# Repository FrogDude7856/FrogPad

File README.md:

# FrogPad
A 12-key hackpad for music with a .91in OLED and a frog-shaped case.

# Features
- Volume and music playback control as default
- 12 Cherry MX compatable mechanical keys
- An OLED that (hopefully) displays your current audio playing (TBD) or does whatever else you want it to display
- A frog shaped case
- Direct connection to PC via USB-C for reduced latency
- A delete key in the center to smash to your hearts content

# Credits/Acknolegements
Thank you to:
- the very nice people in the Hack Club Stardance community (namely #hackpad on the slack), for helping me out with my constant questions
- dob9601, who created the OLED display code I am using to run images (https://github.com/dob9601/qmk-oled-api#client-snippet) and to hopefully display music (https://github.com/dob9601/qmk-oled-api#client-snippet)
- QMK's large database of tutorials, for teaching me how to use their software

# BOM
- 1x Seeed XIAO RP2040 microcontroller
- 1x PCB (see Production folder)
- 2x 3D printed parts: 1x TOP and 1x BOTTOM (See Production folder)
- 12x MX-Style mechanical switches
- 12x Keycaps (I am using blank DSA keycaps)
- 12x 1N4148 through-hole diodes
- 1x 0.91in OLED screen
- 4x M3×16mm screws
- 4x M3×5×4mm heatset inserts
- A sodering iron (for assembly)
- Sanity (optional)
- Paint pens/googly eyes for adding case details and labling keys (optional)

# Progress Images (Screenshots of scematic, PCB, and case on their own)

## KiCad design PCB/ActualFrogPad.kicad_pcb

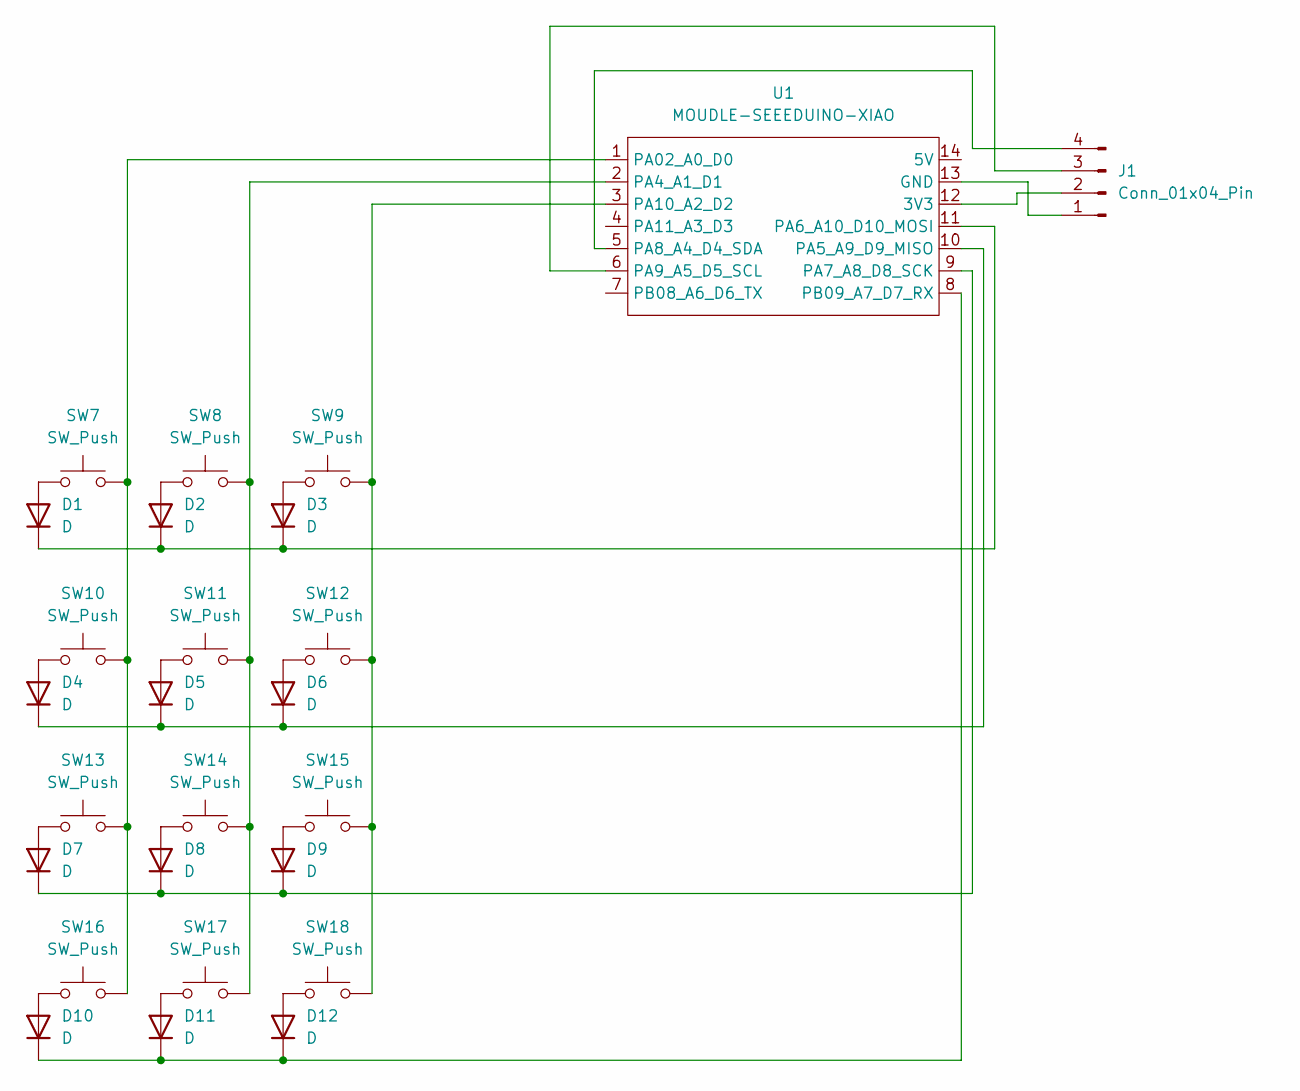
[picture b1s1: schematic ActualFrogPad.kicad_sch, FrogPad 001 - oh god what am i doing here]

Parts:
D1, D2, D3, D4, D5, D6, D7, D8, D9, D10, D11, D12: D; D_DO-35_SOD27_P7.62mm_Horizontal
J1: Conn_01x04_Pin; SSD1306-0.91-OLED-4pin-128x32
SW7, SW8, SW9, SW10, SW11, SW12, SW13, SW14, SW15, SW16, SW17, SW18: SW_Push; SW_Cherry_MX_1.00u_PCB
U1: MOUDLE-SEEEDUINO-XIAO; XIAO-Generic-Hybrid-14P-2.54-21X17.8MM

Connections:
unnamed: D1.2 (A), SW7.1
unnamed: D1.1 (K), D2.1 (K), D3.1 (K), U1.11 (PA6_A10_D10_MOSI)
unnamed: D2.2 (A), SW8.1
unnamed: D3.2 (A), SW9.1
unnamed: D4.2 (A), SW10.1
unnamed: D4.1 (K), D5.1 (K), D6.1 (K), U1.10 (PA5_A9_D9_MISO)
unnamed: D5.2 (A), SW11.1
unnamed: D6.2 (A), SW12.1
unnamed: D7.2 (A), SW13.1
unnamed: D7.1 (K), D8.1 (K), D9.1 (K), U1.9 (PA7_A8_D8_SCK)
unnamed: D8.2 (A), SW14.1
unnamed: D9.2 (A), SW15.1
unnamed: D10.2 (A), SW16.1
unnamed: D10.1 (K), D11.1 (K), D12.1 (K), U1.8 (PB09_A7_D7_RX)
unnamed: D11.2 (A), SW17.1
unnamed: D12.2 (A), SW18.1
unnamed: J1.1, U1.13 (GND)
unnamed: J1.2, U1.12 (3V3)
unnamed: J1.3, U1.6 (PA9_A5_D5_SCL)
unnamed: J1.4, U1.5 (PA8_A4_D4_SDA)
unnamed: SW7.2, SW10.2, SW13.2, SW16.2, U1.1 (PA02_A0_D0)
unnamed: SW8.2, SW11.2, SW14.2, SW17.2, U1.2 (PA4_A1_D1)
unnamed: SW9.2, SW12.2, SW15.2, SW18.2, U1.3 (PA10_A2_D2)

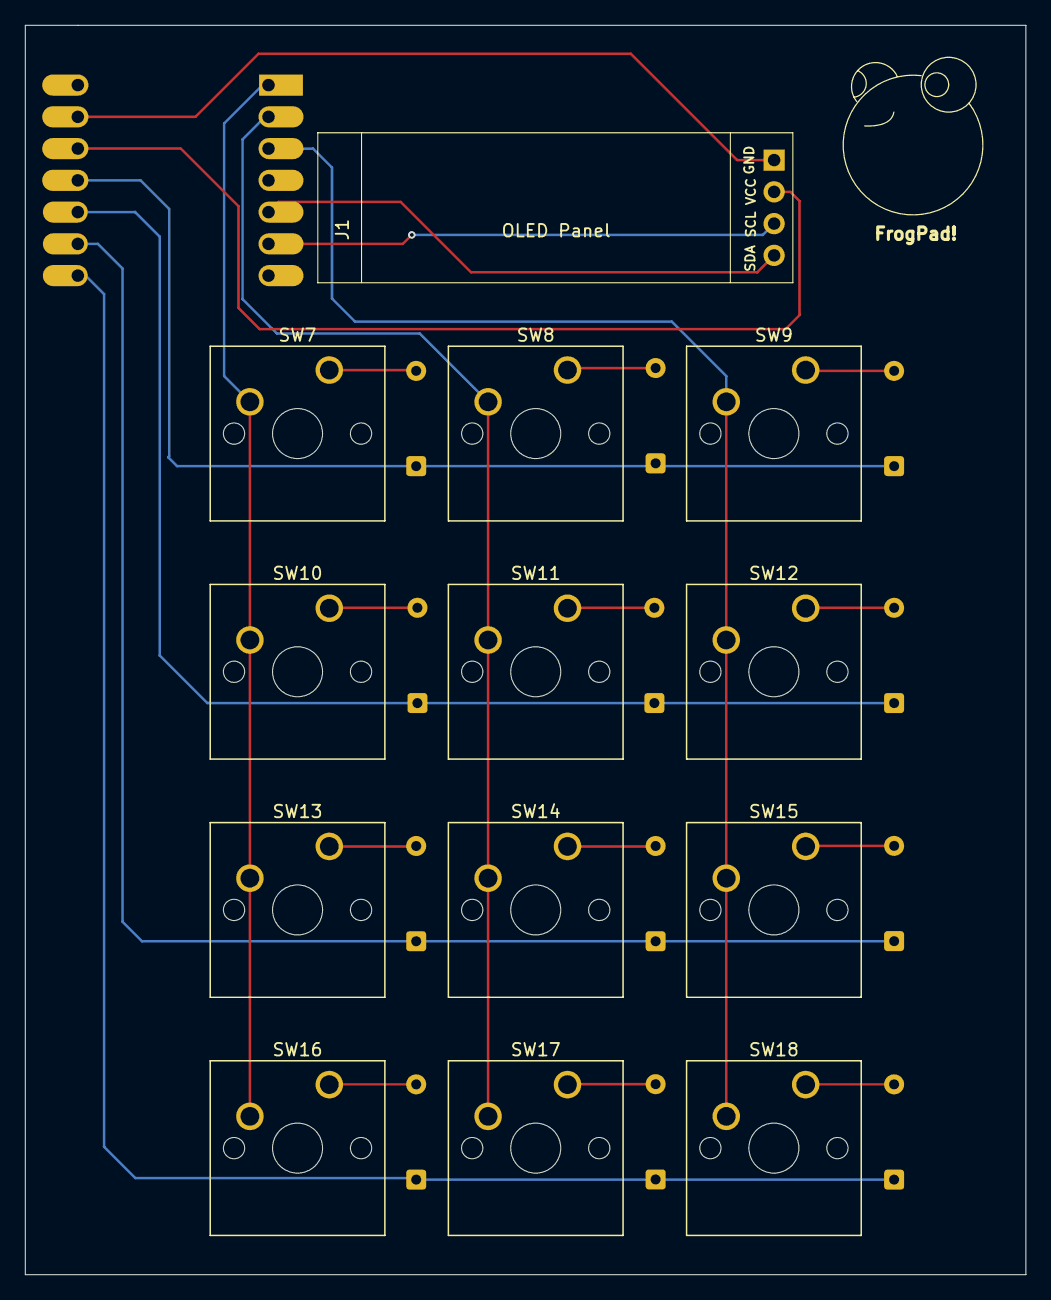
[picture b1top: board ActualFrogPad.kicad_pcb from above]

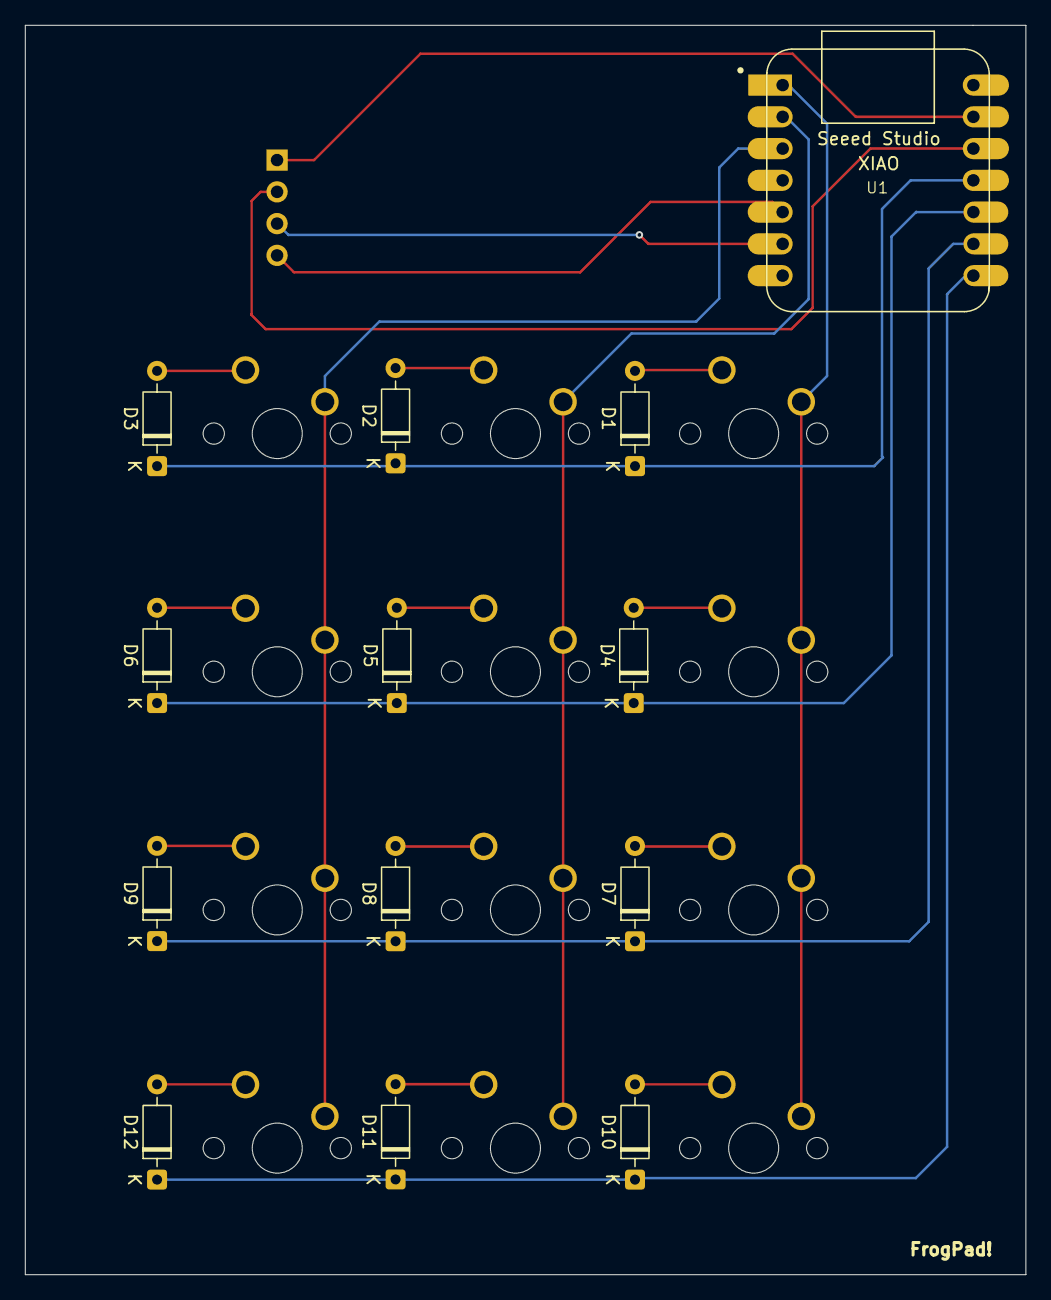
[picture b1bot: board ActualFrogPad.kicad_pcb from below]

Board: 2 copper layers, 80.0 x 99.9 mm, 26 parts (13 on the bottom side), 23 nets.

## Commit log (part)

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2026-06-17 Case and PCB
    Add PCB files (.zip) and case files (.step)
2026-06-17 Update README.md
    fix typo: added period to tagline
2026-06-17 Update LICENSE
    Fix: misclick on license page
2026-06-18 Mass Upload of files + reorg
    - Reorganize files into folders
    - Upload of all required media for Stardance submission
2026-06-18 Update LICENSE (again)
    fix: A SECOND MISCLICK (i'm going insane)
2026-06-18 Update README.md
    Add: images of progress
2026-06-18 Update README.md
    Fix: wrong start screenshot
2026-06-18 Updated file: Render
    Add: updated render file w/ fixed baseplate
2026-06-18 Bottom Panel Update
    Add: USB port on bottom plate
    Fix: parts not properly intersecting
2026-06-18 Update README.md
    Add: BOM
    Remove: Temp. Demo placement
2026-06-18 Update README.md
    Fix: formatting of BOM
2026-06-19 Remove: extraneous CAD file
2026-06-19 Add: PCB schematic and design
